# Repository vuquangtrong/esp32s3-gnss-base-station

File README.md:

# RTK GNSS Base Station using ESP32-S3 and Ublox ZED-F9P

Design and build a RTK GNSS Base Station to provide precise positioning service, which sends RTCM messages over a self-hosted NTRIP web server or an external Radio module, supports micro SD Card storage for post-processing purposes.

This project is developed on top of [ESP32-S3-WROOM-1-N16R8](https://documentation.espressif.com/esp32-s3-wroom-1_wroom-1u_datasheet_en.pdf), with below specifications:

- Xtensa® dual-core 32-bit LX7 microprocessor with single precision FPU, up to 240 MHz
- 384 KB ROM
- 512 KB SRAM + 16 KB SRAM in RTC
- Embedded 8 MB PSRAM (Octal SPI), up to 80 MHz
- Integrated 16 MB Flash (Quad SPI), up to 80 MHz
- 2.4 GHz Wi-Fi (802.11b/g/n, STA/AP/STA+AP, 150 Mbps) and Bluetooth 5 (BLE, Mesh, 2 Mbps)
- SPI, LCD interface, Camera interface, UART, I2C, I2S, remote control, pulse counter, LED PWM, full-speed USB 2.0 OTG, USB Serial/JTAG controller, MCPWM, SD/MMC host controller, GDMA, TWAI® controller (compatible with ISO 11898-1), ADC, touch sensor,temperature sensor, timers and watchdogs
- 36 GPIOs

## Hardware

### Design Tools

Install **KiCad**:

```sh
sudo add-apt-repository ppa:kicad/kicad-9.0-releases
sudo apt update
sudo apt install kicad
```

Extensions:

- Parts from Espressif: <https://github.com/espressif/kicad-libraries>
- Parts from JLCPCB: <https://github.com/CDFER/JLCPCB-Kicad-Library>
- PCB Export to JLCPCB: <https://github.com/Bouni/kicad-jlcpcb-tools>
- PCB RF tools: <https://github.com/easyw/RF-tools-KiCAD>

Parts:

- JLCPCB Parts: <https://jlcpcb.com/parts/> which mainly is from LCSC Parts: <https://www.lcsc.com/>

  - Search for **Stock Type = In Stock** and **Parts Type = Basic | Promotional Extended** and **PCBA Type = Economic**

  - Use `easyeda2kicad` to download symbols, footprints and 3D models from LCSC to KiCAD:

    <details>

    <https://github.com/enduity/easyeda2kicad>>

    Install:

    ``` sh
    cd hardware
    git clone https://github.com/enduity/easyeda2kicad
    cd easyeda2kicad
    python3 -m venv .venv
    source .venv/bin/activate
    pip install .
    ```

    Go back to the hardware project folder, create `libs` folder:

    ```sh
    cd ..
    mkdir -p libs
    ```

    Then download parts from LCSC, for example, ESP32-S3-WROOM-1-N16R8 has LCSCID=C2913202:

    ```sh esp32-s3-gnss-base-station/hardware (.venv)
    easyeda2kicad --lcsc_id C2913202 --full --output ./libs/LCSC --project-relative
    ```

    Add the LCSC libs into KiCAD projects:

    - Goto `Preferences` > `Manage Symbol Libraries`, in Project Specific Libs, add `${KIPRJMOD}/libs/LCSC.kicad_sym`
    - Goto `Preferences` > `Manage Footprint Libraries`, in Project Specific Libs, add `${KIPRJMOD}/libs/LCSC.pretty`

    </details>

### Schematic

**Components**:

| Part                                                                                 | Link                                                                     |
| ------------------------------------------------------------------------------------ | ------------------------------------------------------------------------ |
| Espressif WiFi Module ESP32-S3-WROOM-1-N16R8                                         | <https://jlcpcb.com/partdetail/3198300-ESP32_S3_WROOM_1N16R8/C2913202>   |
| U-blox GNSS Receiver ZED-F9P-04B                                                     | <https://jlcpcb.com/partdetail/UBLOX-ZED_F9P04B/C5120257>                |
| ShouHan Female Micro-B Connector MicroQTJ                                            | <https://jlcpcb.com/partdetail/SHOUHAN-MicroQTJ/C404968>                 |
| SOFNG MicroSD Card Push-Push Connector TF001B                                        | <https://jlcpcb.com/partdetail/SOFNG-TF001B/C125617>                     |
| XKB 125V 3A SPDT Slide Switch SS-12D10L5                                             | <https://jlcpcb.com/partdetail/XKBConnection-SS12D10L5/C319012>          |
| SILICON LABS 3.3V 20mA 1Mbps USB 2.0 Transceiver CP2102-GMR                          | <https://jlcpcb.com/partdetail/SKYWORKS_SILICONLABS-CP2102GMR/C6568>     |
| TOPPOWER 4.2V 450mA 1-Cell Lithium Battery Charger TP4054-42-SOT25R                  | <https://jlcpcb.com/partdetail/33539-TP4054_42SOT25R/C32574>             |
| Silergy Corp 2.7-5.5V 2A Adjustable Buck DC Converter SY8089AAAC                     | <https://jlcpcb.com/partdetail/SilergyCorp-SY8089AAAC/C78988>            |
| Hongjiacheng 2-NPN SOT-363 Bipolar MMDT3904                                          | <https://jlcpcb.com/partdetail/hongjiacheng-MMDT3904/C41375125>          |
| JST 1x2P 2mm Connector B2B-PH-K-S(LF)(SN)                                            | <https://jlcpcb.com/partdetail/JST-B2B_PH_K_S_LF_SN/C131337>             |
| UNI-ROYAL(Uniroyal Elec) 100mW 33Ω 75V 0603 SMD 0603WAF330JT5E                       | <https://jlcpcb.com/partdetail/23867-0603WAF330JT5E/C23140>              |
| UNI-ROYAL(Uniroyal Elec) 100mW 1kΩ 75V 0603 SMD 0603WAF1001T5E                       | <https://jlcpcb.com/partdetail/21904-0603WAF1001T5E/C21190>              |
| UNI-ROYAL(Uniroyal Elec) 100mW 2.2kΩ 75V 0603 SMD 0603WAF2201T5E                     | <https://jlcpcb.com/partdetail/4597-0603WAF2201T5E/C4190>                |
| UNI-ROYAL(Uniroyal Elec) 100mW 10kΩ 75V 0603 SMD 0603WAF1002T5E                      | <https://jlcpcb.com/partdetail/26547-0603WAF1002T5E/C25804>              |
| UNI-ROYAL(Uniroyal Elec) 100mW 150kΩ 75V 0603 SMD 0603WAF1503T5E                     | <https://jlcpcb.com/partdetail/23534-0603WAF1503T5E/C22807>              |
| UNI-ROYAL(Uniroyal Elec) 100mW 680kΩ 75V 0603 SMD 0603WAF6803T5E                     | <https://jlcpcb.com/partdetail/26565-0603WAF6803T5E/C25822>              |
| Samsung Electro-Mechanics 100nF 16V X7R ±10% 0402 Ceramic Capacitors CL05B104KO5NNNC | <https://jlcpcb.com/partdetail/1877-CL05B104KO5NNNC/C1525>               |
| Samsung Electro-Mechanics 10uF 25V X5R ±20% 0603 Ceramic Capacitors CL10A106MA8NRNC  | <https://jlcpcb.com/partdetail/97651-CL10A106MA8NRNC/C96446>             |
| Samsung Electro-Mechanics 22uF 25V X5R ±20% 0805 Ceramic Capacitors CL21A226MAQNNNE  | <https://jlcpcb.com/partdetail/46786-CL21A226MAQNNNE/C45783>             |
| Samsung Electro-Mechanics 47pF 50V C0G ±5% 0603 Ceramic Capacitors CL10C470JB8NNNC   | <https://jlcpcb.com/partdetail/2023-CL10C470JB8NNNC/C1671>               |
| Hubei KENTO Elec 2.4V 20mA 300mcd 40mW 645nm Red Water Clear 0603 LED                | <https://jlcpcb.com/partdetail/Hubei_KENTOElec-KT0603R/C2286>            |
| Sunlord 2.2uH 2A 52mΩ ±20% SMD 4x4mm Power Inductors SWPA4026S2R2MT                  | <https://jlcpcb.com/partdetail/Sunlord-SWPA4026S2R2MT/C96891>            |
| Murata Electronics 110mA 120nH 2.66Ω ±5% 0402 Power Inductors LQW15ANR12J00D         | <https://jlcpcb.com/partdetail/MurataElectronics-LQW15ANR12J00D/C113123> |
| Q&J CR1220 SMD Button And Strip Battery Connector CR1220-2                           | <https://jlcpcb.com/partdetail/QJ-CR12202/C70381>                        |
| BAT WIRELESS 50Ω 6GHz SMB Female Connectors BWSMB-KE                                 | <https://jlcpcb.com/partdetail/BATWIRELESS-BWSMBKE/C5250063>             |

**Schematic**

### PCB Layout

Layers:

- Front Copper: Signal
- Inner 1: GND
- Inner 2: GND
- Back Copper: Signal

RF Path:

- In ZED-F9P Integration manual, it mentions that RF input should ensure RF trace is tuned for 50 Ω to ensure adequate bandwidth and power matching
- Board will be made by JLCPCB, refer their guidance at <https://jlcpcb.com/help/article/User-Guide-to-the-JLCPCB-Impedance-Calculator> to get the trace width, details in [RF Impedance Calculator](hardware/impedance_calculator.png)

PCB Layout:

The rendered images:

<div style="display: flex; gap: 16px;">
  <div style="flex: 1;">
    
  </div>
  <div style="flex: 1;">
    
  </div>
</div>

The final board:

<div style="display: flex; gap: 16px;">
  <div style="flex: 1;">
    
  </div>
  <div style="flex: 1;">
    
  </div>
</div>

------------------------------------------------------------

## Firmware

### Development Tools

- IDE: Visual Studio Code + ESP-IDF Extenstion
- Framework: ESP-IDF for ESP32-S3

### ESP-IDF

Install EIM:

``` sh
echo "deb [trusted=yes] https://dl.espressif.com/dl/eim/apt/ stable main" | sudo tee /etc/apt/sources.list.d/espressif.list
sudo apt update
sudo apt install eim
```

Install ESP-IDF SDK from EIM:

- Install latest STABLE version, at the moment, it is 6.0.2. The online document for ESP32-S3 is at <https://docs.espressif.com/projects/esp-idf/en/v6.0.2/esp32s3/index.html>
- Use default settings

Add OpenOCD udev rules:

``` sh
find ~/.espressif -type f -name "*.rules" -exec sudo cp -v {} /etc/udev/rules.d/ \;
sudo udevadm control --reload-rules
sudo udevadm trigger
```

### SDK Config

``` ini
CONFIG_IDF_TARGET="esp32s3"
CONFIG_BOOTLOADER_LOG_LEVEL_NONE=y
CONFIG_ESPTOOLPY_FLASHMODE_QIO=y
CONFIG_ESPTOOLPY_FLASHSIZE_16MB=y
CONFIG_COMPILER_OPTIMIZATION_PERF=y
CONFIG_ESP_DEFAULT_CPU_FREQ_MHZ_240=y
CONFIG_ESP32S3_INSTRUCTION_CACHE_32KB=y
CONFIG_ESP32S3_INSTRUCTION_CACHE_LINE_32B=y
CONFIG_ESP32S3_DATA_CACHE_64KB=y
CONFIG_ESP32S3_DATA_CACHE_LINE_64B=y
CONFIG_FREERTOS_GENERATE_RUN_TIME_STATS=y
CONFIG_LOG_DYNAMIC_LEVEL_CONTROL=n
CONFIG_LOG_TAG_LEVEL_IMPL_NONE=y
```

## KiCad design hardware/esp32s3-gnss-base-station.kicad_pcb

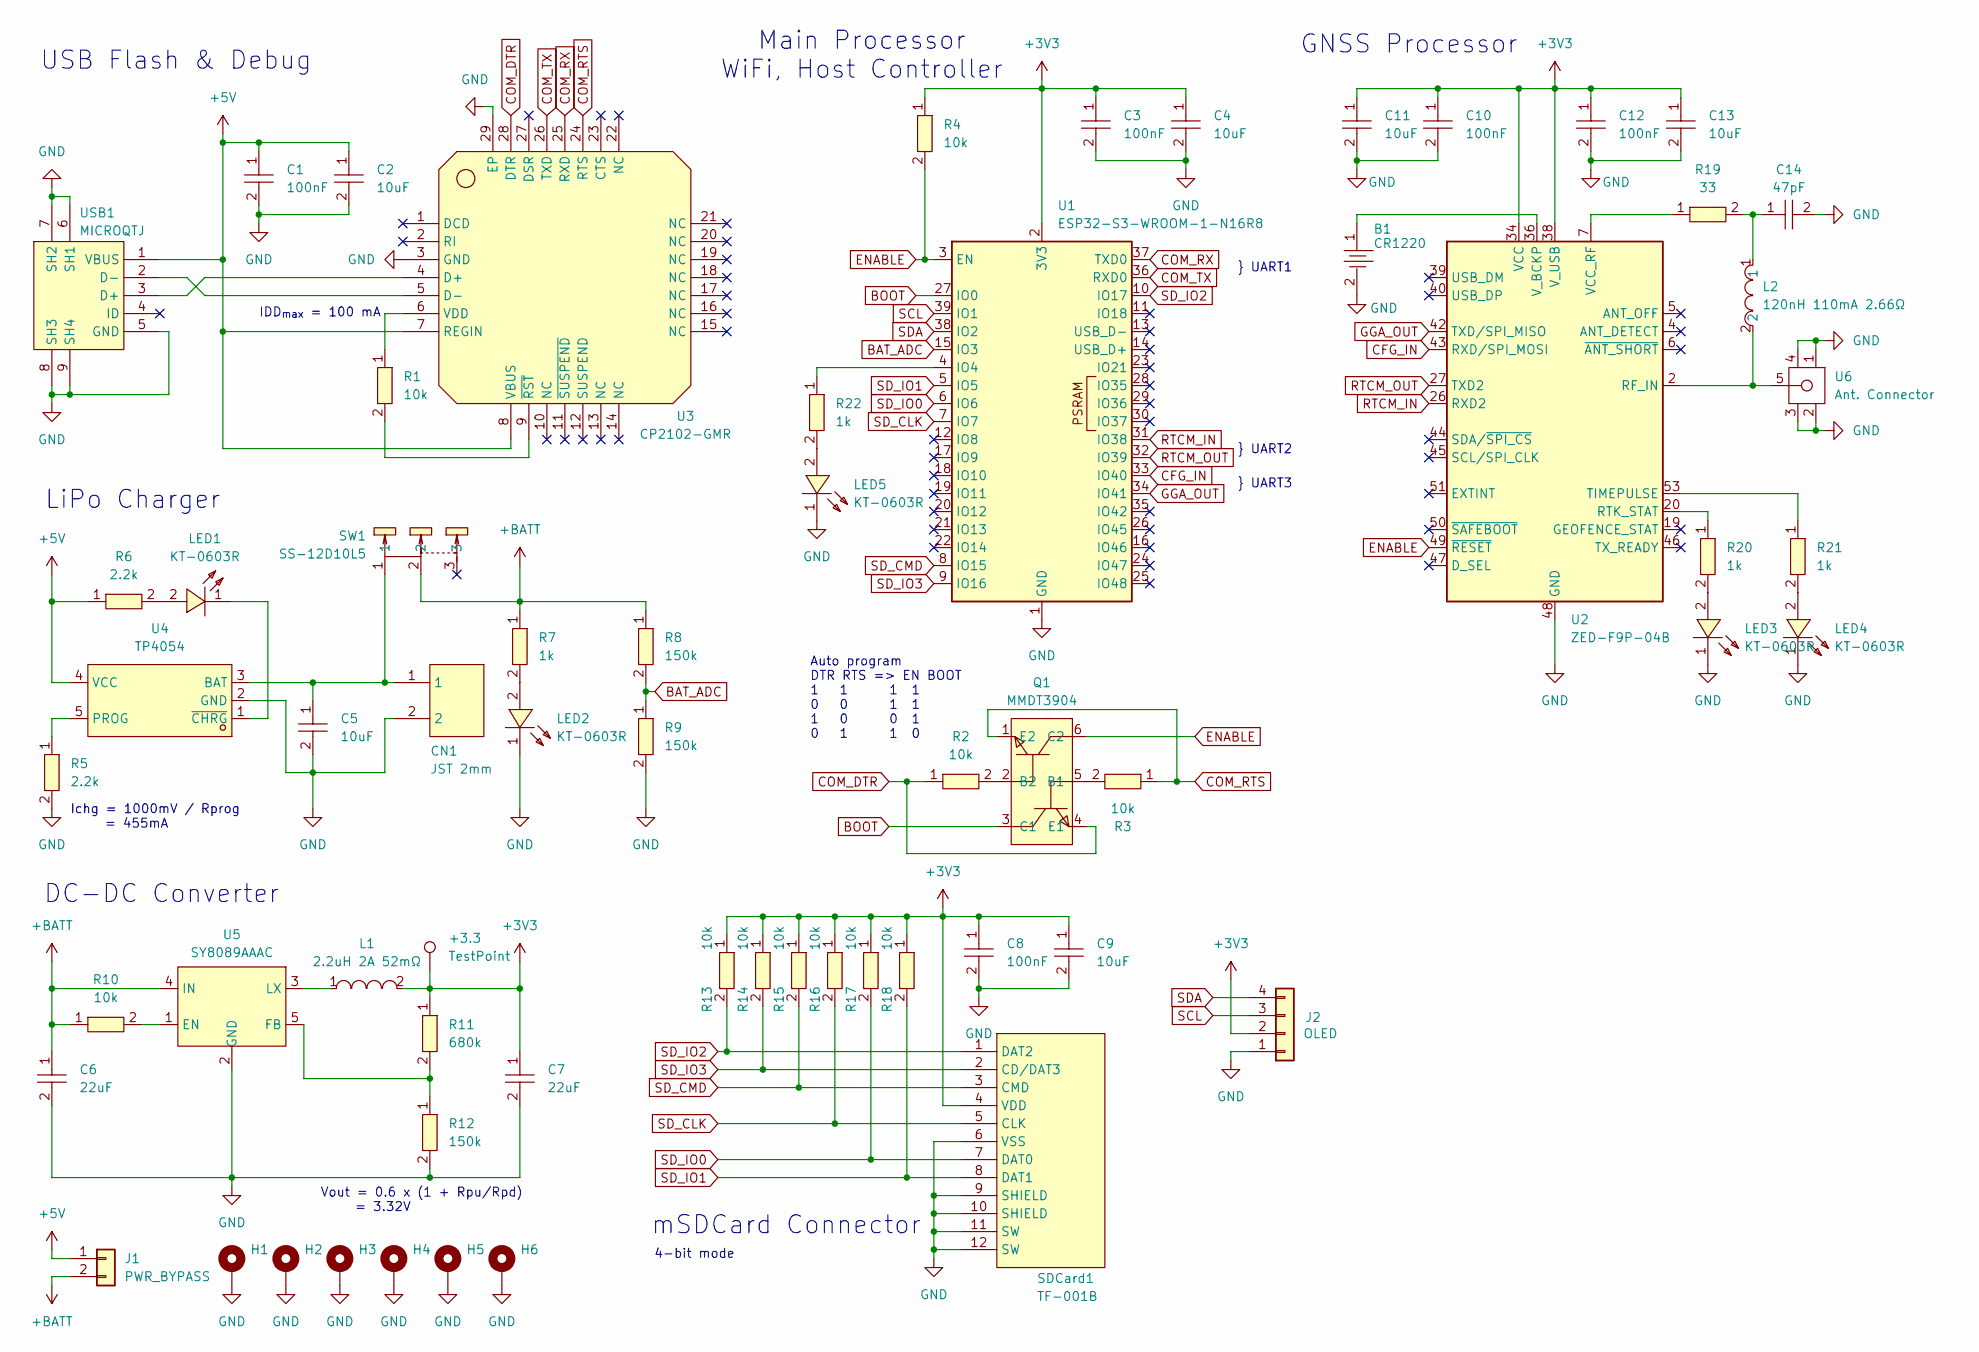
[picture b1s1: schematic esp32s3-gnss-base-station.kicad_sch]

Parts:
+3.3: TestPoint; TestPoint_Pad_D1.5mm
B1: CR1220; BAT-SMD_CR1220-2; LCSC Part C70381
C1, C3, C8, C10, C12: 100nF; C0402; LCSC Part C1525
C2, C4, C5, C9, C11, C13: 10uF; C0603; LCSC Part C96446
C6, C7: 22uF; C0805; LCSC Part C45783
C14: 47pF; C0603; LCSC Part C1671
CN1: JST 2mm; CONN-TH_B2B-PH-K-S; LCSC Part C131337
H1, H2, H3, H4, H5, H6: MountingHole_Pad; MountingHole_2.5mm_Pad
J1: PWR_BYPASS; PinHeader_1x02_P2.54mm_Vertical
J2: OLED; PinHeader_1x04_P2.54mm_Vertical
L1: 2.2uH 2A 52mΩ; IND-SMD_L4.0-W4.0; LCSC Part C96891
L2: 120nH 110mA 2.66Ω; L0402; LCSC Part C113123
LED1, LED2, LED3, LED4, LED5: KT-0603R; LED0603-RD; LCSC Part C2286
Q1: MMDT3904; SOT-363_L2.0-W1.3-P0.65-LS2.1-BR; LCSC Part C41375125
R1, R2, R3, R4, R10, R13, R14, R15, R16, R17, R18: 10k; R0603; LCSC Part C25804
R5, R6: 2.2k; R0603; LCSC Part C4190
R7, R20, R21, R22: 1k; R0603; LCSC Part C21190
R8, R9, R12: 150k; R0603; LCSC Part C22807
R11: 680k; R0603; LCSC Part C25822
R19: 33; R0603; LCSC Part C23140
SDCard1: TF-001B; TF-SMD_TF-001B; LCSC Part C125617
SW1: SS-12D10L5; SW-TH_SS-12D10L5; LCSC Part C319012
U1: ESP32-S3-WROOM-1-N16R8; ESP32-S3-WROOM-1
U2: ZED-F9P-04B; ublox_ZED
U3: CP2102-GMR; WQFN-28_L5.0-W5.0-P0.50-BL-EP3.2; LCSC Part C6568
U4: TP4054; SOT-23-5_L3.0-W1.7-P0.95-LS2.8-BL; LCSC Part C32574
U5: SY8089AAAC; SOT-23-5_L3.0-W1.7-P0.95-LS2.8-BR; LCSC Part C78988
U6: Ant. Connector; SMA-TH_BWMCX-KE; LCSC Part C5137197
USB1: MICROQTJ; MICRO-USB-SMD_MICROQTJ-5P; LCSC Part C404968

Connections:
+3V3: +3.3.1, C3.1, C4.1, C7.1, C8.1, C9.1, C10.1, C11.1, C12.1, C13.1, J2.2, L1.2, R4.1, R11.1, R13.1, R14.1, R15.1, R16.1, R17.1, R18.1, SDCard1.4 (VDD), U1.2 (3V3), U2.33 (VCC), U2.34 (VCC), U2.38 (V_USB)
+5V: C1.1, C2.1, J1.1, R6.1, U3.7 (REGIN), U3.8 (VBUS), U4.4 (VCC), USB1.1 (VBUS)
+BATT: C6.1, J1.2, R7.1, R8.1, R10.1, SW1.2, U5.4 (IN)
BAT_ADC: R8.2, R9.1, U1.15 (IO3)
BOOT: Q1.3 (C1), U1.27 (IO0)
CFG_IN: U1.33 (IO40), U2.43 (RXD/SPI_MOSI)
COM_DTR: Q1.4 (E1), R2.1, U3.28 (DTR)
COM_RTS: Q1.1 (E2), R3.1, U3.24 (RTS)
COM_RX: U1.37 (TXD0), U3.25 (RXD)
COM_TX: U1.36 (RXD0), U3.26 (TXD)
ENABLE: Q1.6 (C2), R4.2, U1.3 (EN), U2.49 (~RESET)
GGA_OUT: U1.34 (IO41), U2.42 (TXD/SPI_MISO)
GND: B1.2, C1.2, C2.2, C3.2, C4.2, C5.2, C6.2, C7.2, C8.2, C9.2, C10.2, C11.2, C12.2, C13.2, C14.2, CN1.2, H1.1, H2.1, H3.1, H4.1, H5.1, H6.1, J2.1, LED2.1, LED3.1, LED4.1, LED5.1, R5.2, R9.2, R12.2, SDCard1.6 (VSS), SDCard1.9 (SHIELD), SDCard1.10 (SHIELD), SDCard1.11 (SW), SDCard1.12 (SW), U1.1 (GND), U1.40 (GND), U1.41 (GND), U2.1 (GND), U2.3 (GND), U2.12 (GND), U2.14 (GND), U2.32 (GND), U2.37 (GND), U2.41 (GND), U2.48 (GND), U2.55 (GND), U3.3 (GND), U3.29 (EP), U4.2 (GND), U5.2 (GND), U6.1, U6.2, U6.3, U6.4, USB1.5 (GND), USB1.6 (SH1), USB1.7 (SH2), USB1.8 (SH3), USB1.9 (SH4)
unnamed: C14.1, L2.1, R19.2
unnamed: LED1.2, R6.2
unnamed: LED2.2, R7.2
unnamed: LED3.2, R20.2
unnamed: LED4.2, R21.2
unnamed: LED5.2, R22.2
unnamed: Q1.5 (B1), R3.2
unnamed: Q1.2 (B2), R2.2
unnamed: R22.1, U1.4 (IO4)
unnamed: L2.2, U2.2 (RF_IN), U6.5
unnamed: R20.1, U2.20 (RTK_STAT)
unnamed: R21.1, U2.53 (TIMEPULSE)
unnamed: R19.1, U2.7 (VCC_RF)
unnamed: B1.1, U2.36 (V_BCKP)
unnamed: U3.4 (D+), USB1.3 (D+)
unnamed: U3.5 (D-), USB1.2 (D-)
unnamed: R1.1, U3.6 (VDD)
unnamed: R1.2, U3.9 (~RST)
unnamed: C5.1, CN1.1, SW1.1, U4.3 (BAT)
unnamed: R5.1, U4.5 (PROG)
unnamed: LED1.1, U4.1 (~CHRG)
unnamed: R10.2, U5.1 (EN)
unnamed: R11.2, R12.1, U5.5 (FB)
unnamed: L1.1, U5.3 (LX)
RTCM_IN: U1.31 (IO38), U2.26 (RXD2)
RTCM_OUT: U1.32 (IO39), U2.27 (TXD2)
SCL: J2.3, U1.39 (IO1)
SDA: J2.4, U1.38 (IO2)
SD_CLK: R16.2, SDCard1.5 (CLK), U1.7 (IO7)
SD_CMD: R15.2, SDCard1.3 (CMD), U1.8 (IO15)
SD_IO0: R17.2, SDCard1.7 (DAT0), U1.6 (IO6)
SD_IO1: R18.2, SDCard1.8 (DAT1), U1.5 (IO5)
SD_IO2: R13.2, SDCard1.1 (DAT2), U1.10 (IO17)
SD_IO3: R14.2, SDCard1.2 (CD/DAT3), U1.9 (IO16)

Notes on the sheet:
Ichg = 1000mV / Rprog = 455mA
Vout = 0.6 x (1 + Rpu/Rpd) = 3.32V
Auto program DTR RTS => EN BOOT 1 1 1 1 0 0 1 1 1 0 0 1 0 1 1 0
LiPo Charger
} UART1
} UART3
} UART2
4-bit mode
Main Processor WiFi, Host Controller
USB Flash & Debug
DC-DC Converter
mSDCard Connector
IDD_{max} = 100 mA
GNSS Processor

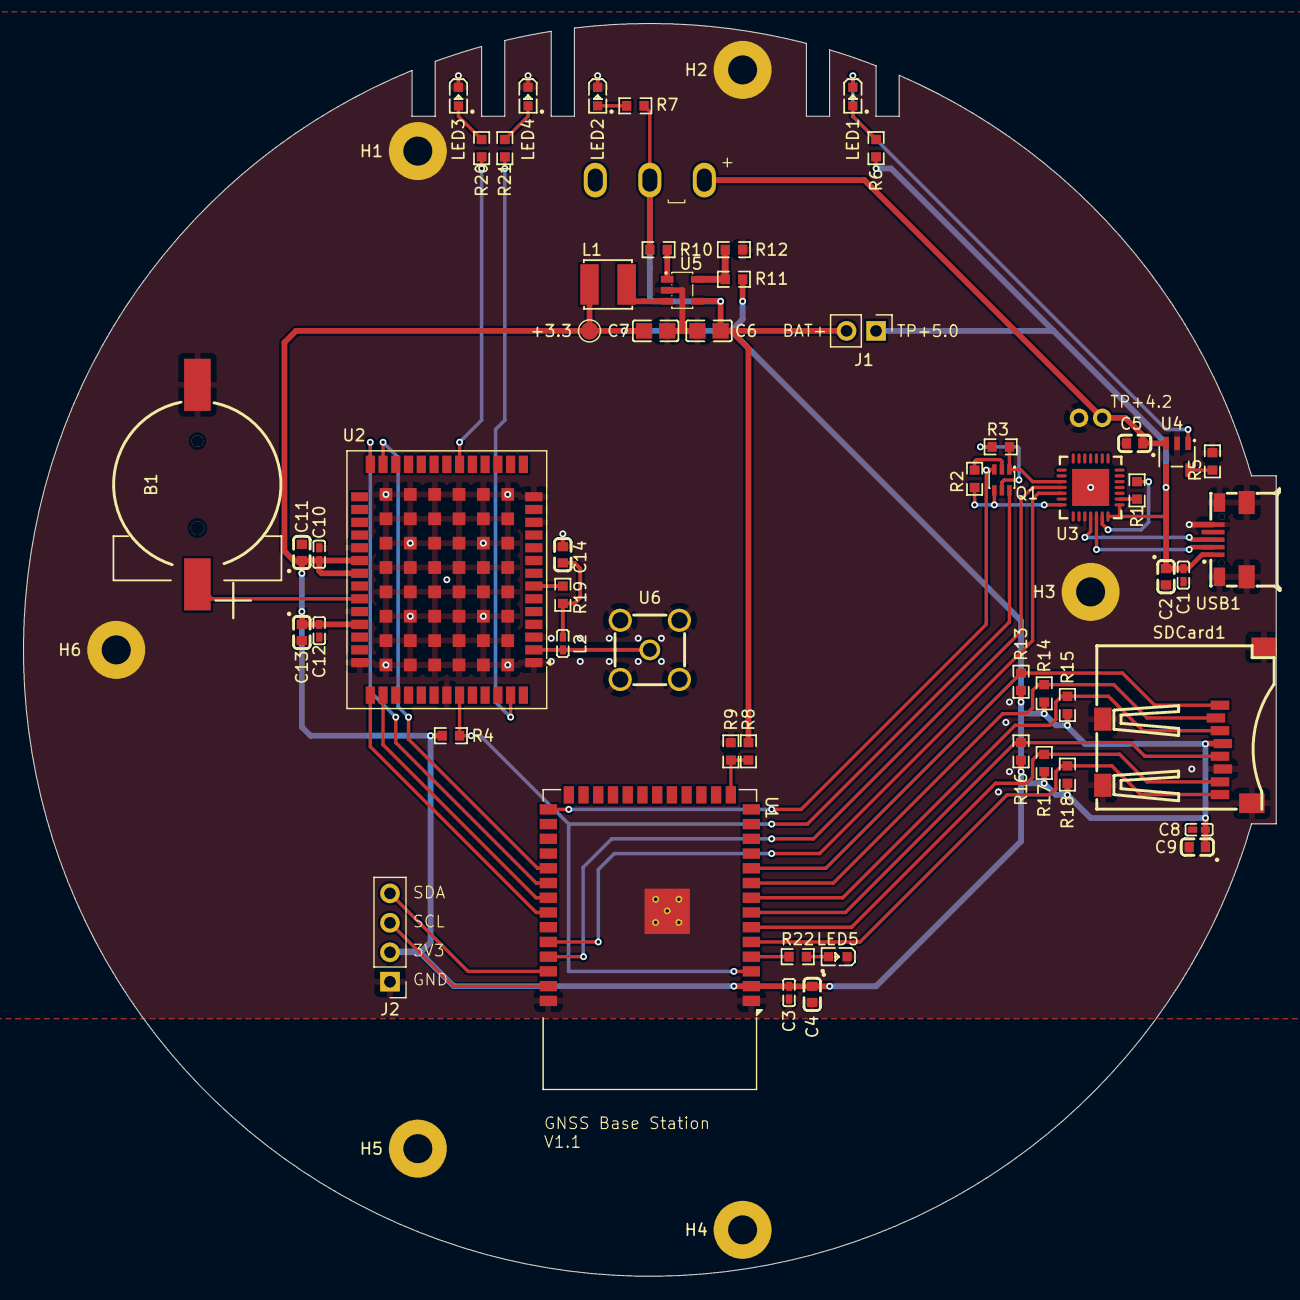
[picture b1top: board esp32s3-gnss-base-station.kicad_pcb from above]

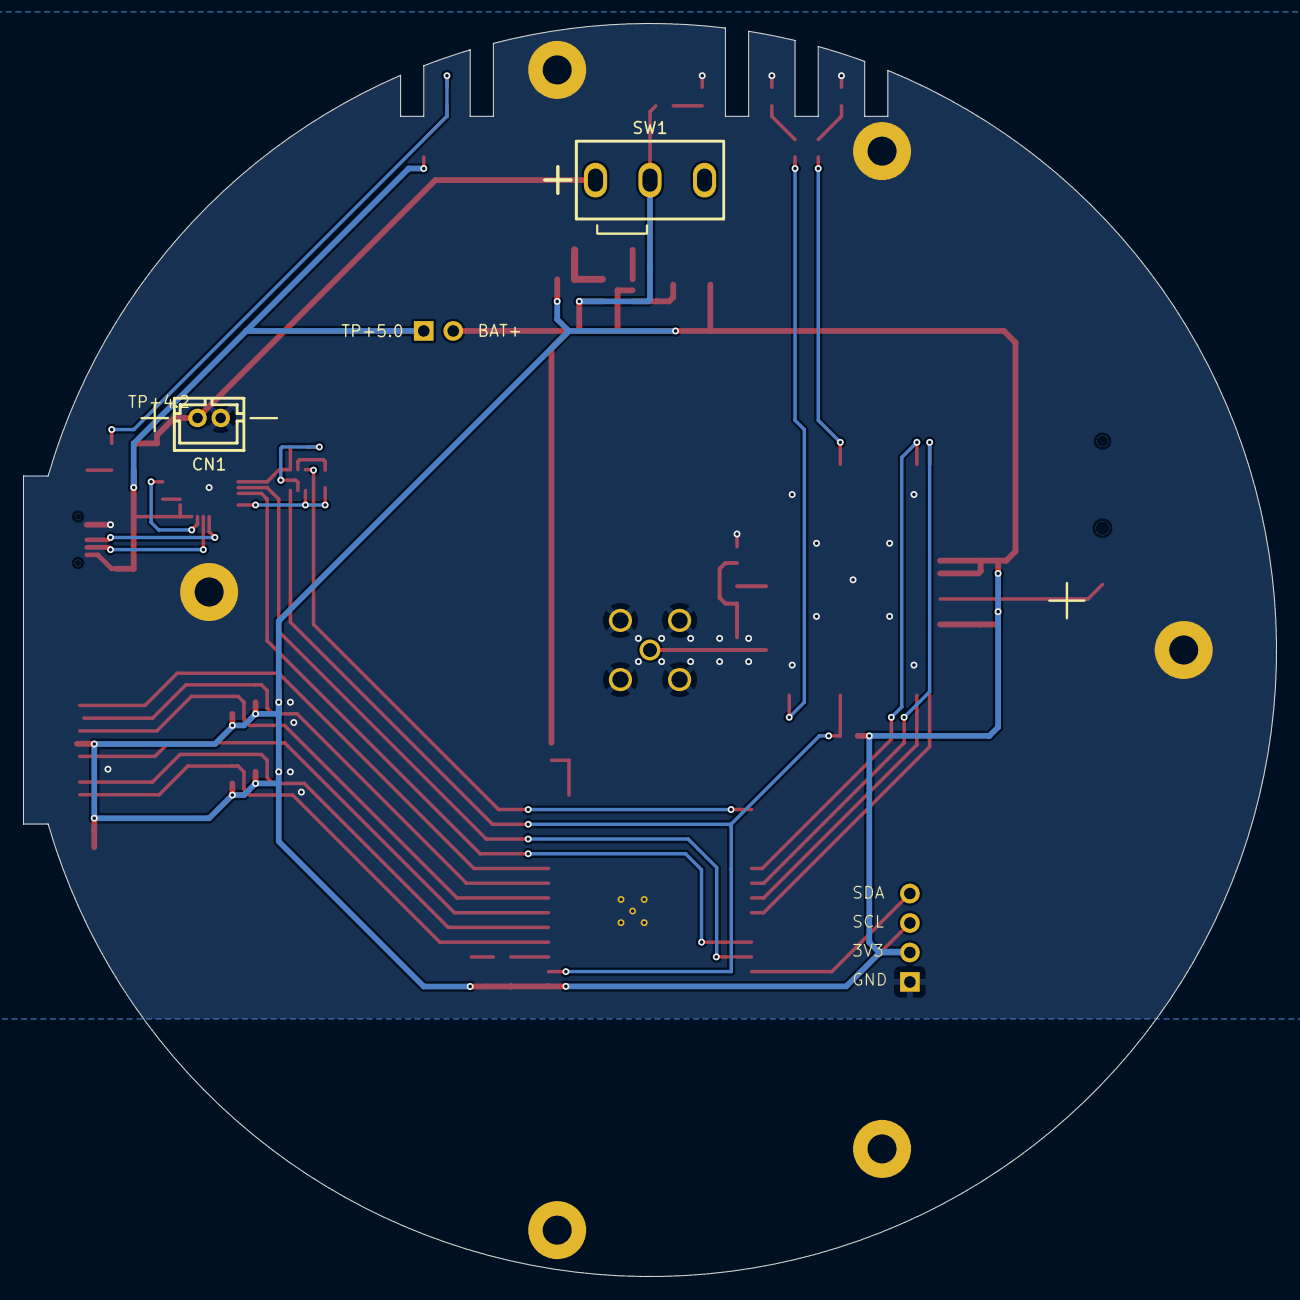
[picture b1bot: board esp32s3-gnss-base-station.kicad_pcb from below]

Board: 4 copper layers, 108.0 x 108.0 mm, 64 parts (2 on the bottom side), 47 nets.

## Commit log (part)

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2025-11-25 Init project
2025-11-25 Init KiCAD project with board shape
2025-12-12 Add KiCAD Schematic v0.1
2025-12-17 Add KicCAD PCB Layout v0.1 and order on JLCPCB
2026-01-14 Update PCB and export some images
2026-01-20 Init ESP-IDF project
2026-01-23 Add Factory Test
2026-01-24 Add Factory Test image
2026-03-13 Update PCB screenshots
2026-03-16 Prepare for firmware development
2026-03-16 Firmware 1.0 with Ntrip Client and Server
